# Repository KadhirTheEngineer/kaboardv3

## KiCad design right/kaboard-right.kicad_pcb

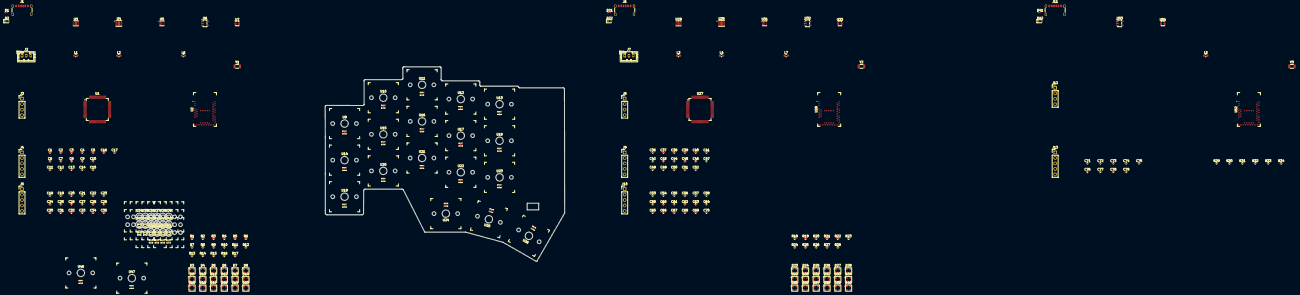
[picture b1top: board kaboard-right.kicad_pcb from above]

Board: 2 copper layers, 231 parts (0 on the bottom side), 178 nets, no tracks yet.

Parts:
C1, C36: 1u BQ IN; C_0402_1005Metric
C2, C37: 10u SYS; C_0402_1005Metric
C3, C38: 1u BAT; C_0402_1005Metric
C4, C39: 10u TPS IN; C_0402_1005Metric
C5, C40: 10u 3V3; C_0402_1005Metric
C6, C41: 100n STM VDD; C_0402_1005Metric
C7, C42: 100n STM VDDA; C_0402_1005Metric
C8, C43, C73: 100n nRF VDD; C_0402_1005Metric
C9, C44, C74: 100n nRF VDDH; C_0402_1005Metric
C10, C45, C75: 100n nRF VBUS; C_0402_1005Metric
C11, C46, C76: 12p NRF XL1; C_0402_1005Metric
C12, C47, C77: 12p NRF XL2; C_0402_1005Metric
C13, C48: 10u RGB IN; C_0402_1005Metric
C14, C49: 47u LED 5V; C_0402_1005Metric
C15, C50: 100n LED bulk; C_0402_1005Metric
C16, C51, C78: 1u OLED VCC; C_0402_1005Metric
C17, C52, C79: 100n OLED VCC; C_0402_1005Metric
C18: 100n TMAG A01; C_0402_1005Metric
C19: 100n TMAG A02; C_0402_1005Metric
C20: 100n TMAG A03; C_0402_1005Metric
C21: 100n TMAG A04; C_0402_1005Metric
C22: 100n TMAG A05; C_0402_1005Metric
C23: 100n TMAG A06; C_0402_1005Metric
C24: 100n TMAG A07; C_0402_1005Metric
C25: 100n TMAG A08; C_0402_1005Metric
C26: 100n TMAG A09; C_0402_1005Metric
C27: 100n TMAG A10; C_0402_1005Metric
C28: 100n TMAG A11; C_0402_1005Metric
C29: 100n TMAG A12; C_0402_1005Metric
C30: 100n TMAG A13; C_0402_1005Metric
C31: 100n TMAG A14; C_0402_1005Metric
C32: 100n TMAG A15; C_0402_1005Metric
C33: 100n TMAG A16; C_0402_1005Metric
C34: 100n TMAG A17; C_0402_1005Metric
C35: 100n TMAG A18; C_0402_1005Metric
C53: 100n TMAG B01; C_0402_1005Metric
C54: 100n TMAG B02; C_0402_1005Metric
C55: 100n TMAG B03; C_0402_1005Metric
C56: 100n TMAG B04; C_0402_1005Metric
C57: 100n TMAG B05; C_0402_1005Metric
C58: 100n TMAG B06; C_0402_1005Metric
C59: 100n TMAG B07; C_0402_1005Metric
C60: 100n TMAG B08; C_0402_1005Metric
C61: 100n TMAG B09; C_0402_1005Metric
C62: 100n TMAG B10; C_0402_1005Metric
C63: 100n TMAG B11; C_0402_1005Metric
C64: 100n TMAG B12; C_0402_1005Metric
C65: 100n TMAG B13; C_0402_1005Metric
C66: 100n TMAG B14; C_0402_1005Metric
C67: 100n TMAG B15; C_0402_1005Metric
C68: 100n TMAG B16; C_0402_1005Metric
C69: 100n TMAG B17; C_0402_1005Metric
C70: 100n TMAG B18; C_0402_1005Metric
C71: 10u USB 5V IN; C_0402_1005Metric
C72: 10u RX 3V3; C_0402_1005Metric
D1, D21, D41: ESD441DPYR USB VBUS; D_0201_0603Metric
D2: LEFT STATUS LED; LED_0603_1608Metric
D3: WL-ICLED A01; U_Wurth_WL-ICLED_1312020030000
D4: WL-ICLED A02; U_Wurth_WL-ICLED_1312020030000
D5: WL-ICLED A03; U_Wurth_WL-ICLED_1312020030000
D6: WL-ICLED A04; U_Wurth_WL-ICLED_1312020030000
D7: WL-ICLED A05; U_Wurth_WL-ICLED_1312020030000
D8: WL-ICLED A06; U_Wurth_WL-ICLED_1312020030000
D9: WL-ICLED A07; U_Wurth_WL-ICLED_1312020030000
D10: WL-ICLED A08; U_Wurth_WL-ICLED_1312020030000
D11: WL-ICLED A09; U_Wurth_WL-ICLED_1312020030000
D12: WL-ICLED A10; U_Wurth_WL-ICLED_1312020030000
D13: WL-ICLED A11; U_Wurth_WL-ICLED_1312020030000
D14: WL-ICLED A12; U_Wurth_WL-ICLED_1312020030000
D15: WL-ICLED A13; U_Wurth_WL-ICLED_1312020030000
D16: WL-ICLED A14; U_Wurth_WL-ICLED_1312020030000
D17: WL-ICLED A15; U_Wurth_WL-ICLED_1312020030000
D18: WL-ICLED A16; U_Wurth_WL-ICLED_1312020030000
D19: WL-ICLED A17; U_Wurth_WL-ICLED_1312020030000
D20: WL-ICLED A18; U_Wurth_WL-ICLED_1312020030000
D22: RIGHT STATUS LED; LED_0603_1608Metric
D23: WL-ICLED B01; U_Wurth_WL-ICLED_1312020030000
D24: WL-ICLED B02; U_Wurth_WL-ICLED_1312020030000
D25: WL-ICLED B03; U_Wurth_WL-ICLED_1312020030000
D26: WL-ICLED B04; U_Wurth_WL-ICLED_1312020030000
D27: WL-ICLED B05; U_Wurth_WL-ICLED_1312020030000
D28: WL-ICLED B06; U_Wurth_WL-ICLED_1312020030000
D29: WL-ICLED B07; U_Wurth_WL-ICLED_1312020030000
D30: WL-ICLED B08; U_Wurth_WL-ICLED_1312020030000
D31: WL-ICLED B09; U_Wurth_WL-ICLED_1312020030000
D32: WL-ICLED B10; U_Wurth_WL-ICLED_1312020030000
D33: WL-ICLED B11; U_Wurth_WL-ICLED_1312020030000
D34: WL-ICLED B12; U_Wurth_WL-ICLED_1312020030000
D35: WL-ICLED B13; U_Wurth_WL-ICLED_1312020030000
D36: WL-ICLED B14; U_Wurth_WL-ICLED_1312020030000
D37: WL-ICLED B15; U_Wurth_WL-ICLED_1312020030000
D38: WL-ICLED B16; U_Wurth_WL-ICLED_1312020030000
D39: WL-ICLED B17; U_Wurth_WL-ICLED_1312020030000
D40: WL-ICLED B18; U_Wurth_WL-ICLED_1312020030000
D42: STATUS LED; LED_0603_1608Metric
J1, J6, J11: USB_C_Receptacle_PowerOnly_6P; USB_C_Receptacle_GCT_USB4125-xx-x-0190_6P_TopMnt_Horizontal
J2, J7: AS584070 BATTERY / 10k NTC; JST_PH_B3B-PH-K_1x03_P2.00mm_Vertical
J3, J8, J12: SH1106 1.3in 4-wire OLED; PinHeader_1x04_P2.54mm_Vertical
J4, J9: STM32 SWD; PinHeader_1x05_P2.54mm_Vertical
J5, J10: nRF SWD; PinHeader_1x05_P2.54mm_Vertical
J13: Receiver nRF SWD; PinHeader_1x05_P2.54mm_Vertical
L1, L3: 2.2uH TPS63031; L_0603_1608Metric
L2, L4: 1uH RGB BOOST; L_0603_1608Metric
L5, L6, L7: 10uH nRF DCDC; L_0603_1608Metric
R1, R15, R29: 5.1k USB CC1; R_0402_1005Metric
R2, R16, R30: 5.1k USB CC2; R_0402_1005Metric
R3, R17: 18k BQ ILIM/VSET; R_0402_1005Metric
R4, R18: 845R BQ ISET; R_0402_1005Metric
R5, R19, R31: 10k nRF RESET pullup; R_0402_1005Metric
R6, R20: 10k BOOT0 pulldown; R_0402_1005Metric
R7, R21, R32: 4.7k I2C SDA pullup; R_0402_1005Metric
R8, R22, R33: 4.7k I2C SCL pullup; R_0402_1005Metric
R9, R23: 1M BAT_SENSE top; R_0402_1005Metric
R10, R24: 330k BAT_SENSE bottom; R_0402_1005Metric
R11, R25: 330R RGB data; R_0402_1005Metric
R12, R26: 732k RGB FB top; R_0402_1005Metric
R13, R27: 100k RGB FB bottom; R_0402_1005Metric
R14, R28, R34: 1k STATUS LED; R_0402_1005Metric
U1, U27: STM32G431RBTx; LQFP-64_10x10mm_P0.5mm
U2, U28, U52: MDBT50Q-1MV2; Raytac_MDBT50Q
U3, U29: BQ25185DLHR; Texas_DLH0010A_WSON-10-1EP_2.2x2mm_P0.4mm_EP0.9x1.5mm
U4, U30: TPS63031DSK; WSON-10-1EP_2.5x2.5mm_P0.5mm_EP1.2x2mm
U5, U31: TPS61022 RGB BOOST; Texas_RWU0007A_VQFN-7_2x2mm_P0.5mm
U6, U32: 74AHCT1G125; SOT-23-5
U7, U33, U54: TPS22919DCK; SOT-363_SC-70-6
U9: TMAG5253 A01; Kaboard_JadePro_TMAG5253
U10: TMAG5253 A02; Kaboard_JadePro_TMAG5253
U11: TMAG5253 A03; Kaboard_JadePro_TMAG5253
U12: TMAG5253 A04; Kaboard_JadePro_TMAG5253
U13: TMAG5253 A05; Kaboard_JadePro_TMAG5253
U14: TMAG5253 A06; Kaboard_JadePro_TMAG5253
U15: TMAG5253 A07; Kaboard_JadePro_TMAG5253
U16: TMAG5253 A08; Kaboard_JadePro_TMAG5253
U17: TMAG5253 A09; Kaboard_JadePro_TMAG5253
U18: TMAG5253 A10; Kaboard_JadePro_TMAG5253
U19: TMAG5253 A11; Kaboard_JadePro_TMAG5253
U20: TMAG5253 A12; Kaboard_JadePro_TMAG5253
U21: TMAG5253 A13; Kaboard_JadePro_TMAG5253
U22: TMAG5253 A14; Kaboard_JadePro_TMAG5253
U23: TMAG5253 A15; Kaboard_JadePro_TMAG5253
U24: TMAG5253 A16; Kaboard_JadePro_TMAG5253
U25: TMAG5253 A17; Kaboard_JadePro_TMAG5253
U26: TMAG5253 A18; Kaboard_JadePro_TMAG5253
U34: TMAG5253 B01; Kaboard_JadePro_TMAG5253
U35: TMAG5253 B02; Kaboard_JadePro_TMAG5253
U36: TMAG5253 B03; Kaboard_JadePro_TMAG5253
U37: TMAG5253 B04; Kaboard_JadePro_TMAG5253
U38: TMAG5253 B05; Kaboard_JadePro_TMAG5253
U39: TMAG5253 B06; Kaboard_JadePro_TMAG5253
U40: TMAG5253 B07; Kaboard_JadePro_TMAG5253
U41: TMAG5253 B08; Kaboard_JadePro_TMAG5253
U42: TMAG5253 B09; Kaboard_JadePro_TMAG5253
U43: TMAG5253 B10; Kaboard_JadePro_TMAG5253
U44: TMAG5253 B11; Kaboard_JadePro_TMAG5253
U45: TMAG5253 B12; Kaboard_JadePro_TMAG5253
U46: TMAG5253 B13; Kaboard_JadePro_TMAG5253
U47: TMAG5253 B14; Kaboard_JadePro_TMAG5253
U48: TMAG5253 B15; Kaboard_JadePro_TMAG5253
U49: TMAG5253 B16; Kaboard_JadePro_TMAG5253
U50: TMAG5253 B17; Kaboard_JadePro_TMAG5253
U51: TMAG5253 B18; Kaboard_JadePro_TMAG5253
U53: AP2112K-3.3; SOT-23-5
Y1, Y2, Y3: 32.768kHz; Crystal_SMD_3215-2Pin_3.2x1.5mm

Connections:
/L_3V3: C5.1, C6.1, C7.1, C8.1, C9.1, C10.1, C13.1, C18.1, C19.1, C20.1, C21.1, C22.1, C23.1, C24.1, C25.1, C26.1, C27.1, C28.1, C29.1, C30.1, C31.1, C32.1, C33.1, C34.1, C35.1, J4.1, J5.1, L2.1, L6.2, R5.2, R7.1, R8.1, U1.1 (VBAT), U1.16 (VDD), U1.28 (VREF+), U1.29 (VDDA), U1.32 (VDD), U1.48 (VDD), U1.64 (VDD), U2.28 (VDD), U2.30 (VDDH), U2.32 (VBUS), U4.1 (VOUT), U4.10 (FB), U5.7 (VIN), U7.1 (IN), U9.1 (VCC), U10.1 (VCC), U11.1 (VCC), U12.1 (VCC), U13.1 (VCC), U14.1 (VCC), U15.1 (VCC), U16.1 (VCC), U17.1 (VCC), U18.1 (VCC), U19.1 (VCC), U20.1 (VCC), U21.1 (VCC), U22.1 (VCC), U23.1 (VCC), U24.1 (VCC), U25.1 (VCC), U26.1 (VCC)
/L_BAT: C3.1, J2.1, R9.1, U3.2 (BAT)
/L_BAT_SENSE: R9.2, R10.1, U2.10 (P0.29)
/L_BOOT0: R6.1, U1.61 (PB8)
/L_BQ_ILIM: R3.1, U3.7 (ILIM/VSET)
/L_BQ_ISET: R4.1, U3.8 (ISET)
/L_DISPLAY_EN: U2.49 (P0.25), U7.3 (ON)
/L_DISPLAY_SCL: J3.3, R8.2, U2.19 (P0.26)
/L_DISPLAY_SDA: J3.4, R7.2, U2.16 (P0.27)
/L_GND: C1.2, C2.2, C3.2, C4.2, C5.2, C6.2, C7.2, C8.2, C9.2, C10.2, C11.2, C12.2, C13.2, C14.2, C15.2, C16.2, C17.2, C18.2, C19.2, C20.2, C21.2, C22.2, C23.2, C24.2, C25.2, C26.2, C27.2, C28.2, C29.2, C30.2, C31.2, C32.2, C33.2, C34.2, C35.2, D1.2 (GND), D2.1 (K), D3.4 (VSS), D4.4 (VSS), D5.4 (VSS), D6.4 (VSS), D7.4 (VSS), D8.4 (VSS), D9.4 (VSS), D10.4 (VSS), D11.4 (VSS), D12.4 (VSS), D13.4 (VSS), D14.4 (VSS), D15.4 (VSS), D16.4 (VSS), D17.4 (VSS), D18.4 (VSS), D19.4 (VSS), D20.4 (VSS), J1.A12 (GND), J1.B12 (GND), J1.SH (SHIELD), J2.3, J3.2, J4.2, J5.2, R1.2, R2.2, R3.2, R4.2, R6.2, R10.2, R13.2, U1.15 (VSS), U1.27 (VSSA), U1.31 (VSS), U1.47 (VSS), U1.63 (VSS), U2.1 (GND), U2.2 (GND), U2.15 (GND), U2.33 (GND), U2.55 (GND), U3.4 (/CE), U3.5 (GND), U3.11 (EP), U4.3 (PGND), U4.7 (PS/SYNC), U4.9 (GND), U4.11 (PGND), U5.1 (GND), U5.6 (MODE), U6.1, U6.3 (GND), U7.2 (GND), U9.2 (GND), U9.5 (EP), U10.2 (GND), U10.5 (EP), U11.2 (GND), U11.5 (EP), U12.2 (GND), U12.5 (EP), U13.2 (GND), U13.5 (EP), U14.2 (GND), U14.5 (EP), U15.2 (GND), U15.5 (EP), U16.2 (GND), U16.5 (EP), U17.2 (GND), U17.5 (EP), U18.2 (GND), U18.5 (EP), U19.2 (GND), U19.5 (EP), U20.2 (GND), U20.5 (EP), U21.2 (GND), U21.5 (EP), U22.2 (GND), U22.5 (EP), U23.2 (GND), U23.5 (EP), U24.2 (GND), U24.5 (EP), U25.2 (GND), U25.5 (EP), U26.2 (GND), U26.5 (EP)
/L_HALL_EN_A: U1.38 (PC6), U9.3 (EN), U10.3 (EN), U11.3 (EN), U12.3 (EN), U13.3 (EN), U14.3 (EN)
/L_HALL_EN_B: U1.39 (PC7), U15.3 (EN), U16.3 (EN), U17.3 (EN), U18.3 (EN), U19.3 (EN), U20.3 (EN)
/L_HALL_EN_C: U1.40 (PC8), U21.3 (EN), U22.3 (EN), U23.3 (EN), U24.3 (EN), U25.3 (EN), U26.3 (EN)
/L_HALL_OUT_01: U1.8 (PC0), U9.4 (OUT)
/L_HALL_OUT_02: U1.9 (PC1), U10.4 (OUT)
/L_HALL_OUT_03: U1.10 (PC2), U11.4 (OUT)
/L_HALL_OUT_04: U1.11 (PC3), U12.4 (OUT)
/L_HALL_OUT_05: U1.12 (PA0), U13.4 (OUT)
/L_HALL_OUT_06: U1.13 (PA1), U14.4 (OUT)
/L_HALL_OUT_07: U1.14 (PA2), U15.4 (OUT)
/L_HALL_OUT_08: U1.17 (PA3), U16.4 (OUT)
/L_HALL_OUT_09: U1.18 (PA4), U17.4 (OUT)
/L_HALL_OUT_10: U1.19 (PA5), U18.4 (OUT)
/L_HALL_OUT_11: U1.20 (PA6), U19.4 (OUT)
/L_HALL_OUT_12: U1.21 (PA7), U20.4 (OUT)
/L_HALL_OUT_13: U1.22 (PC4), U21.4 (OUT)
/L_HALL_OUT_14: U1.23 (PC5), U22.4 (OUT)
/L_HALL_OUT_15: U1.24 (PB0), U23.4 (OUT)
/L_HALL_OUT_16: U1.25 (PB1), U24.4 (OUT)
/L_HALL_OUT_17: U1.26 (PB2), U25.4 (OUT)
/L_HALL_OUT_18: U1.33 (PB11), U26.4 (OUT)
/L_LED_5V: C14.1, C15.1, D3.1 (VDD), D4.1 (VDD), D5.1 (VDD), D6.1 (VDD), D7.1 (VDD), D8.1 (VDD), D9.1 (VDD), D10.1 (VDD), D11.1 (VDD), D12.1 (VDD), D13.1 (VDD), D14.1 (VDD), D15.1 (VDD), D16.1 (VDD), D17.1 (VDD), D18.1 (VDD), D19.1 (VDD), D20.1 (VDD), R12.1, U5.3 (VOUT), U5.4 (FB), U6.5 (VCC)
/L_NRF_DCCH: L6.1, U2.31 (DCCH)
/L_NRF_RESET_N: J5.5, R5.1, U2.40 (P0.18)
/L_NRF_XL1: C11.1, U2.17 (P0.00), Y1.1
/L_NRF_XL2: C12.1, U2.18 (P0.01), Y1.2
/L_NTC: J2.2, U3.6 (TS/MR)
/L_OLED_VCC: C16.1, C17.1, J3.1, U7.6 (OUT)
/L_RGB_DATA_3V3: U1.42 (PA8), U6.2
/L_RGB_DATA_5V: R11.1, U6.4
/L_RGB_DIN_01: D3.2 (DIN), R11.2
/L_RGB_DIN_07: D8.3 (DOUT), D9.2 (DIN)
/L_RGB_DIN_13: D14.3 (DOUT), D15.2 (DIN)
/L_RGB_FB: R12.2, R13.1
/L_RGB_PWR_EN: U1.43 (PA9), U5.5 (EN)
/L_RGB_SW: L2.2, U5.2 (SW)
/L_SPI_CS_N: U1.51 (PA15), U2.44 (P0.20)
/L_SPI_MISO: U1.53 (PC11), U2.46 (P0.22)
/L_SPI_MOSI: U1.54 (PC12), U2.43 (P0.21)
/L_SPI_SCK: U1.52 (PC10), U2.42 (P0.19)
/L_STATUS_LED: R14.1, U2.48 (P0.24)
/L_STATUS_LED_A: D2.2 (A), R14.2
/L_STM_DATA_READY: U1.30 (PB10), U2.36 (P0.14)
/L_STM_RESET_N: J4.5, U1.7 (PG10)
/L_STM_WAKE_NRF: U1.41 (PC9), U2.37 (P0.13)
/L_SWCLK_NRF: J5.4, U2.53 (SWDCLK)
/L_SWCLK_STM: J4.4, U1.50 (PA14)
/L_SWDIO_NRF: J5.3, U2.51 (SWDIO)
/L_SWDIO_STM: J4.3, U1.49 (PA13)
/L_SYS: C2.1, C4.1, U3.1 (SYS), U4.5 (VIN), U4.6 (EN), U4.8 (VINA)
/L_TPS_L1: L1.1, U4.4 (L1)
/L_TPS_L2: L1.2, U4.2 (L2)
/L_USB_CC1: J1.A5 (CC1), R1.1
/L_USB_CC2: J1.B5 (CC2), R2.1
/L_USB_VBUS: C1.1, D1.1 (IO), J1.A9 (VBUS), J1.B9 (VBUS), U3.10 (IN)
/RX_3V3: C72.1, C73.1, C74.1, C75.1, J13.1, L5.2, R31.2, R32.1, R33.1, U52.28 (VDD), U52.30 (VDDH), U52.32 (VBUS), U53.5 (VOUT), U54.1 (IN)
/RX_DISPLAY_EN: U52.49 (P0.25), U54.3 (ON)
/RX_DISPLAY_SCL: J12.3, R33.2, U52.19 (P0.26)
/RX_DISPLAY_SDA: J12.4, R32.2, U52.16 (P0.27)
/RX_GND: C71.2, C72.2, C73.2, C74.2, C75.2, C76.2, C77.2, C78.2, C79.2, D41.2 (GND), D42.1 (K), J11.A12 (GND), J11.B12 (GND), J11.SH (SHIELD), J12.2, J13.2, R29.2, R30.2, U52.1 (GND), U52.2 (GND), U52.15 (GND), U52.33 (GND), U52.55 (GND), U53.2 (GND), U54.2 (GND)
/RX_NRF_DCCH: L5.1, U52.31 (DCCH)
/RX_NRF_RESET_N: J13.5, R31.1, U52.40 (P0.18)
/RX_NRF_XL1: C76.1, U52.17 (P0.00), Y3.1
/RX_NRF_XL2: C77.1, U52.18 (P0.01), Y3.2
/RX_OLED_VCC: C78.1, C79.1
/RX_STATUS_LED: R34.1, U52.48 (P0.24)
/RX_STATUS_LED_A: D42.2 (A), R34.2
/RX_SWCLK: J13.4, U52.53 (SWDCLK)
/RX_SWDIO: J13.3, U52.51 (SWDIO)
/RX_USB_CC1: J11.A5 (CC1), R29.1
/RX_USB_CC2: J11.B5 (CC2), R30.1
/RX_USB_VBUS: C71.1, D41.1 (IO), J11.A9 (VBUS), J11.B9 (VBUS), U53.1 (VIN), U53.3 (EN)
/R_3V3: C40.1, C41.1, C42.1, C43.1, C44.1, C45.1, C48.1, C53.1, C54.1, C55.1, C56.1, C57.1, C58.1, C59.1, C60.1, C61.1, C62.1, C63.1, C64.1, C65.1, C66.1, C67.1, C68.1, C69.1, C70.1, J9.1, J10.1, L4.1, L7.2, R19.2, R21.1, R22.1, U27.1 (VBAT), U27.16 (VDD), U27.28 (VREF+), U27.29 (VDDA), U27.32 (VDD), U27.48 (VDD), U27.64 (VDD), U28.28 (VDD), U28.30 (VDDH), U28.32 (VBUS), U30.1 (VOUT), U30.10 (FB), U31.7 (VIN), U33.1 (IN), U34.1 (VCC), U35.1 (VCC), U36.1 (VCC), U37.1 (VCC), U38.1 (VCC), U39.1 (VCC), U40.1 (VCC), U41.1 (VCC), U42.1 (VCC), U43.1 (VCC), U44.1 (VCC), U45.1 (VCC), U46.1 (VCC), U47.1 (VCC), U48.1 (VCC), U49.1 (VCC), U50.1 (VCC), U51.1 (VCC)
/R_BAT: C38.1, J7.1, R23.1, U29.2 (BAT)
/R_BAT_SENSE: R23.2, R24.1, U28.10 (P0.29)
/R_BOOT0: R20.1, U27.61 (PB8)
/R_BQ_ILIM: R17.1, U29.7 (ILIM/VSET)
/R_BQ_ISET: R18.1, U29.8 (ISET)
/R_DISPLAY_EN: U28.49 (P0.25), U33.3 (ON)
/R_DISPLAY_SCL: J8.3, R22.2, U28.19 (P0.26)
/R_DISPLAY_SDA: J8.4, R21.2, U28.16 (P0.27)
/R_GND: C36.2, C37.2, C38.2, C39.2, C40.2, C41.2, C42.2, C43.2, C44.2, C45.2, C46.2, C47.2, C48.2, C49.2, C50.2, C51.2, C52.2, C53.2, C54.2, C55.2, C56.2, C57.2, C58.2, C59.2, C60.2, C61.2, C62.2, C63.2, C64.2, C65.2, C66.2, C67.2, C68.2, C69.2, C70.2, D21.2 (GND), D22.1 (K), D23.4 (VSS), D24.4 (VSS), D25.4 (VSS), D26.4 (VSS), D27.4 (VSS), D28.4 (VSS), D29.4 (VSS), D30.4 (VSS), D31.4 (VSS), D32.4 (VSS), D33.4 (VSS), D34.4 (VSS), D35.4 (VSS), D36.4 (VSS), D37.4 (VSS), D38.4 (VSS), D39.4 (VSS), D40.4 (VSS), J6.A12 (GND), J6.B12 (GND), J6.SH (SHIELD), J7.3, J8.2, J9.2, J10.2, R15.2, R16.2, R17.2, R18.2, R20.2, R24.2, R27.2, U27.15 (VSS), U27.27 (VSSA), U27.31 (VSS), U27.47 (VSS), U27.63 (VSS), U28.1 (GND), U28.2 (GND), U28.15 (GND), U28.33 (GND), U28.55 (GND), U29.4 (/CE), U29.5 (GND), U29.11 (EP), U30.3 (PGND), U30.7 (PS/SYNC), U30.9 (GND), U30.11 (PGND), U31.1 (GND), U31.6 (MODE), U32.1, U32.3 (GND), U33.2 (GND), U34.2 (GND), U34.5 (EP), U35.2 (GND), U35.5 (EP), U36.2 (GND), U36.5 (EP), U37.2 (GND), U37.5 (EP), U38.2 (GND), U38.5 (EP), U39.2 (GND), U39.5 (EP), U40.2 (GND), U40.5 (EP), U41.2 (GND), U41.5 (EP), U42.2 (GND), U42.5 (EP), U43.2 (GND), U43.5 (EP), U44.2 (GND), U44.5 (EP), U45.2 (GND), U45.5 (EP), U46.2 (GND), U46.5 (EP), U47.2 (GND), U47.5 (EP), U48.2 (GND), U48.5 (EP), U49.2 (GND), U49.5 (EP), U50.2 (GND), U50.5 (EP), U51.2 (GND), U51.5 (EP)
/R_HALL_EN_A: U27.38 (PC6), U34.3 (EN), U35.3 (EN), U36.3 (EN), U37.3 (EN), U38.3 (EN), U39.3 (EN)
/R_HALL_EN_B: U27.39 (PC7), U40.3 (EN), U41.3 (EN), U42.3 (EN), U43.3 (EN), U44.3 (EN), U45.3 (EN)
/R_HALL_EN_C: U27.40 (PC8), U46.3 (EN), U47.3 (EN), U48.3 (EN), U49.3 (EN), U50.3 (EN), U51.3 (EN)
/R_HALL_OUT_01: U27.8 (PC0), U34.4 (OUT)
/R_HALL_OUT_02: U27.9 (PC1), U35.4 (OUT)
/R_HALL_OUT_03: U27.10 (PC2), U36.4 (OUT)
/R_HALL_OUT_04: U27.11 (PC3), U37.4 (OUT)
/R_HALL_OUT_05: U27.12 (PA0), U38.4 (OUT)
/R_HALL_OUT_06: U27.13 (PA1), U39.4 (OUT)
/R_HALL_OUT_07: U27.14 (PA2), U40.4 (OUT)
/R_HALL_OUT_08: U27.17 (PA3), U41.4 (OUT)
/R_HALL_OUT_09: U27.18 (PA4), U42.4 (OUT)
/R_HALL_OUT_10: U27.19 (PA5), U43.4 (OUT)
/R_HALL_OUT_11: U27.20 (PA6), U44.4 (OUT)
/R_HALL_OUT_12: U27.21 (PA7), U45.4 (OUT)
/R_HALL_OUT_13: U27.22 (PC4), U46.4 (OUT)
/R_HALL_OUT_14: U27.23 (PC5), U47.4 (OUT)
/R_HALL_OUT_15: U27.24 (PB0), U48.4 (OUT)
/R_HALL_OUT_16: U27.25 (PB1), U49.4 (OUT)
/R_HALL_OUT_17: U27.26 (PB2), U50.4 (OUT)
/R_HALL_OUT_18: U27.33 (PB11), U51.4 (OUT)
/R_LED_5V: C49.1, C50.1, D23.1 (VDD), D24.1 (VDD), D25.1 (VDD), D26.1 (VDD), D27.1 (VDD), D28.1 (VDD), D29.1 (VDD), D30.1 (VDD), D31.1 (VDD), D32.1 (VDD), D33.1 (VDD), D34.1 (VDD), D35.1 (VDD), D36.1 (VDD), D37.1 (VDD), D38.1 (VDD), D39.1 (VDD), D40.1 (VDD), R26.1, U31.3 (VOUT), U31.4 (FB), U32.5 (VCC)
/R_NRF_DCCH: L7.1, U28.31 (DCCH)
/R_NRF_RESET_N: J10.5, R19.1, U28.40 (P0.18)
/R_NRF_XL1: C46.1, U28.17 (P0.00), Y2.1
/R_NRF_XL2: C47.1, U28.18 (P0.01), Y2.2
/R_NTC: J7.2, U29.6 (TS/MR)
/R_OLED_VCC: C51.1, C52.1, J8.1, U33.6 (OUT)
/R_RGB_DATA_3V3: U27.42 (PA8), U32.2
/R_RGB_DATA_5V: R25.1, U32.4
/R_RGB_DIN_01: D23.2 (DIN), R25.2
/R_RGB_DIN_07: D28.3 (DOUT), D29.2 (DIN)
/R_RGB_DIN_13: D34.3 (DOUT), D35.2 (DIN)
/R_RGB_FB: R26.2, R27.1
/R_RGB_PWR_EN: U27.43 (PA9), U31.5 (EN)
/R_RGB_SW: L4.2, U31.2 (SW)
/R_SPI_CS_N: U27.51 (PA15), U28.44 (P0.20)
/R_SPI_MISO: U27.53 (PC11), U28.46 (P0.22)
/R_SPI_MOSI: U27.54 (PC12), U28.43 (P0.21)
/R_SPI_SCK: U27.52 (PC10), U28.42 (P0.19)
/R_STATUS_LED: R28.1, U28.48 (P0.24)
/R_STATUS_LED_A: D22.2 (A), R28.2
/R_STM_DATA_READY: U27.30 (PB10), U28.36 (P0.14)
/R_STM_RESET_N: J9.5, U27.7 (PG10)
/R_STM_WAKE_NRF: U27.41 (PC9), U28.37 (P0.13)
/R_SWCLK_NRF: J10.4, U28.53 (SWDCLK)
/R_SWCLK_STM: J9.4, U27.50 (PA14)
/R_SWDIO_NRF: J10.3, U28.51 (SWDIO)
/R_SWDIO_STM: J9.3, U27.49 (PA13)
/R_SYS: C37.1, C39.1, U29.1 (SYS), U30.5 (VIN), U30.6 (EN), U30.8 (VINA)
/R_TPS_L1: L3.1, U30.4 (L1)
/R_TPS_L2: L3.2, U30.2 (L2)
/R_USB_CC1: J6.A5 (CC1), R15.1
/R_USB_CC2: J6.B5 (CC2), R16.1
/R_USB_VBUS: C36.1, D21.1 (IO), J6.A9 (VBUS), J6.B9 (VBUS), U29.10 (IN)
unnamed: D3.3 (DOUT), D4.2 (DIN)
unnamed: D4.3 (DOUT), D5.2 (DIN)
unnamed: D5.3 (DOUT), D6.2 (DIN)
unnamed: D6.3 (DOUT), D7.2 (DIN)
unnamed: D7.3 (DOUT), D8.2 (DIN)
unnamed: D9.3 (DOUT), D10.2 (DIN)
unnamed: D10.3 (DOUT), D11.2 (DIN)
unnamed: D11.3 (DOUT), D12.2 (DIN)
unnamed: D12.3 (DOUT), D13.2 (DIN)
unnamed: D13.3 (DOUT), D14.2 (DIN)
unnamed: D15.3 (DOUT), D16.2 (DIN)
unnamed: D16.3 (DOUT), D17.2 (DIN)
unnamed: D17.3 (DOUT), D18.2 (DIN)
unnamed: D18.3 (DOUT), D19.2 (DIN)
unnamed: D19.3 (DOUT), D20.2 (DIN)
unnamed: D23.3 (DOUT), D24.2 (DIN)
unnamed: D24.3 (DOUT), D25.2 (DIN)
unnamed: D25.3 (DOUT), D26.2 (DIN)
unnamed: D26.3 (DOUT), D27.2 (DIN)
unnamed: D27.3 (DOUT), D28.2 (DIN)
unnamed: D29.3 (DOUT), D30.2 (DIN)
unnamed: D30.3 (DOUT), D31.2 (DIN)
unnamed: D31.3 (DOUT), D32.2 (DIN)
unnamed: D32.3 (DOUT), D33.2 (DIN)
unnamed: D33.3 (DOUT), D34.2 (DIN)
unnamed: D35.3 (DOUT), D36.2 (DIN)
unnamed: D36.3 (DOUT), D37.2 (DIN)
unnamed: D37.3 (DOUT), D38.2 (DIN)
unnamed: D38.3 (DOUT), D39.2 (DIN)
unnamed: D39.3 (DOUT), D40.2 (DIN)
unnamed: J12.1, U54.6 (OUT)
